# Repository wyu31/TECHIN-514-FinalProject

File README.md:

# TECHIN-514-FinalProject
This GitHub repository is for my TECHIN-514 final project and all my related files will be uploaded and updated to it.

## System Architecture with Diagram
### Slide 1 - Introduction
**Project Title**  
Finger Drumbeat

**Explanation**  
This is an IoT device set to add drum beats using hand gestures, allowing users to engage in existing music.

Generally, I want to achieve:
1. Different **fingertip accelerations** produce different **Stepper-motor-driven gauge needle** swing accelerations and different drum beat loudnesses (with **Speaker & Amplifier**).
2. Different **components of the drum** (Bass Drum, Tom-Tom Drum, Snare drum, Crash Cymbal, Ride Cymbal, Hi-Hat) are played under different **gestures**.
3. **OLED** screen displays the component currently being played.
4. **LED Array** randomly displays rhythm animation
5. **Button** can switch the random animations on the LED Array

**General Sketch**  

### Slide 2 - Sensor Device
In this part, the enclosure is divided into two parts: fingertip and wrist. The fingertip enclosure contains the MPU6050, and the wrist enclosure contains the ESP32 processor and battery.

MPU6050 and ESP32 will detect and analyze diffeerent fingertip accelerations for different needle swing accelerations and drumbeat volumes.

MPU6050 and ESP32 will also detect and analyze different gestures as different drum components (such as ass Drum, Tom-Tom Drum, Snare drum, Crash Cymbal, Ride Cymbal, Hi-Hat).

1. Sensor: MPU6050 accelerometer and gyroscope to detect hand accelerations and gestures
2. Processor: XIAO-ESP32-S3
3. Wireless link:  XIAO-ESP32-S3 has a bluetooth module inside
4. Power: Lithium Ion Polymer Battery Ideal For Feathers
5. Enclosure:(Shown on Sketch) 
6. Custom PCB: will be based on the sensor, battery & enclosure size

### Slide 3 - Display Device
The shaking acceleration of the stepper motor pointer depends on the acceleration of the finger; the intensity of the sound and enhanced sound also depends on the acceleration of the finger.

The LED array will randomly play flowing animations to reflect the linkage of audio and vision; touch the button to switch animations.

The OLED screen will display the names of the components of the drum set selected under the current gesture.

1. Stepper-motor-driven gauge needle:  Show the intensity and volume of the drumming. More forceful gestures could push the needle further, indicating a higher intensity and volume.
2. Processor: XIAO-ESP32-S3
3. LED Array:  LED Array randomly displays rhythm animation
4. Button: Capacitive touch button to switch animations
5. Enclosure:(Shown on Sketch) 
6. Custom PCB: will be based on the sensors & enclosure size
7. Battery: Lithium Ion Polymer Battery Ideal For Feathers
8. Displays: OLED - Text info of the type of drum sound currently selected

### Slide 4 - Figure & Diagram

**Device Communication Figure**

**Workflow Diagram**

**Display Device Arch**

## PCB Lab
### Processer: XIAO-ESP32-S3

### Sensor: XIAO-ESP32-S3

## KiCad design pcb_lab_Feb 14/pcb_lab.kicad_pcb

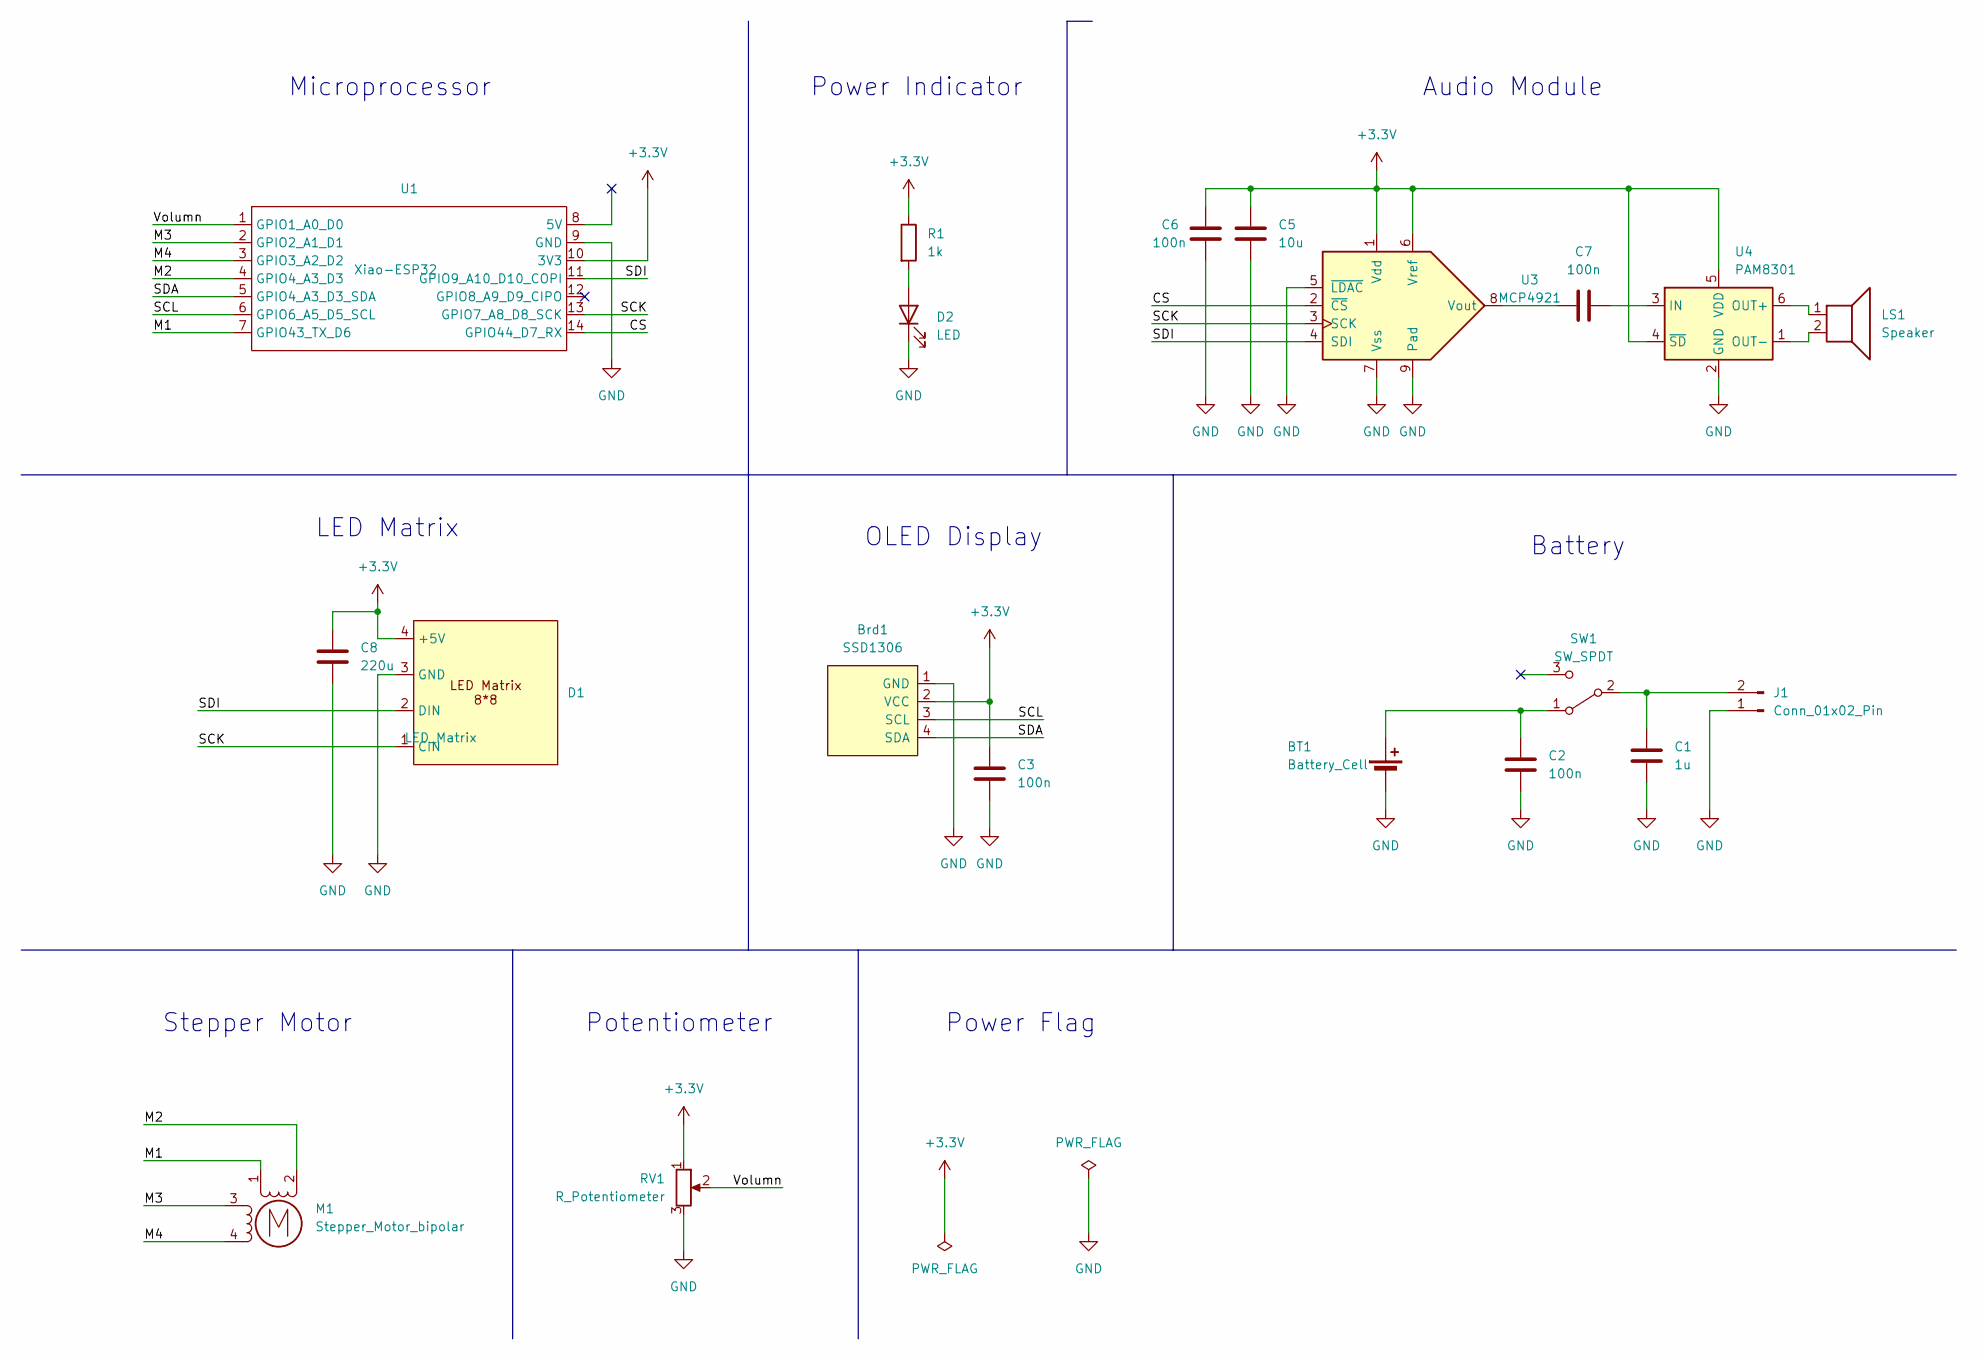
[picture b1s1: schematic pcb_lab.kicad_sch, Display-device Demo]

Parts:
BT1: Battery_Cell; JST_XA_B02B-XASK-1-A_1x02_P2.50mm_Vertical
Brd1: SSD1306; 128x64OLED
C1: 1u; C_0603_1608Metric_Pad1.08x0.95mm_HandSolder
C2, C3, C6, C7: 100n; C_0603_1608Metric_Pad1.08x0.95mm_HandSolder
C5: 10u; CP_EIA-1608-08_AVX-J_Pad1.25x1.05mm_HandSolder
C8: 220u; CP_Radial_D6.3mm_P2.50mm
D1: LED_Matrix; PinSocket_1x04_P2.54mm_Horizontal
D2: LED; LED_0603_1608Metric_Pad1.05x0.95mm_HandSolder
J1: Conn_01x02_Pin; JST_NV_B02P-NV_1x02_P5.00mm_Vertical
LS1: Speaker; JST_NV_B02P-NV_1x02_P5.00mm_Vertical
M1: Stepper_Motor_bipolar; X27_stepper_motor
R1: 1k; R_0603_1608Metric_Pad0.98x0.95mm_HandSolder
RV1: R_Potentiometer; Potentiometer_Piher_PC-16_Single_Horizontal
SW1: SW_SPDT; JST_EH_B3B-EH-A_1x03_P2.50mm_Vertical
U1: Xiao-ESP32; XIAO_ESP32_SENSE
U3: MCP4921; DFN-8-1EP_3x2mm_P0.5mm_EP1.3x1.5mm
U4: PAM8301; SOT-23-6

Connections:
+3.3V: Brd1.2 (VCC), C3.1, C5.1, C6.1, C8.1, D1.4 (+5V), R1.1, RV1.1, U1.10 (3V3), U3.1 (Vdd), U3.6 (Vref), U4.4 (~SD), U4.5 (VDD)
/CS: U1.14 (GPIO44_D7_RX), U3.2 (~CS)
/M1: M1.1, U1.7 (GPIO43_TX_D6)
/M2: M1.2 (-), U1.4 (GPIO4_A3_D3)
/M3: M1.3, U1.2 (GPIO2_A1_D1)
/M4: M1.4, U1.3 (GPIO3_A2_D2)
/SCK: D1.1 (CIN), U1.13 (GPIO7_A8_D8_SCK), U3.3 (SCK)
/SCL: Brd1.3 (SCL), U1.6 (GPIO6_A5_D5_SCL)
/SDA: Brd1.4 (SDA), U1.5 (GPIO4_A3_D3_SDA)
/SDI: D1.2 (DIN), U1.11 (GPIO9_A10_D10_COPI), U3.4 (SDI)
/Volumn: RV1.2, U1.1 (GPIO1_A0_D0)
GND: BT1.2 (-), Brd1.1 (GND), C1.2, C2.2, C3.2, C5.2, C6.2, C8.2, D1.3 (GND), D2.1 (K), J1.1, RV1.3, U1.9 (GND), U3.5 (~LDAC), U3.7 (Vss), U3.9 (Pad), U4.2 (GND)
unnamed: BT1.1 (+), C2.1, SW1.1 (A)
unnamed: D2.2 (A), R1.2
unnamed: C1.1, J1.2, SW1.2 (B)
unnamed: C7.1, U3.8 (Vout)
unnamed: C7.2, U4.3 (IN)
unnamed: LS1.1, U4.6 (OUT+)
unnamed: LS1.2, U4.1 (OUT-)

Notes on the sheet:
Audio Module
Power Flag
Stepper Motor
Microprocessor
Power Indicator
Battery
OLED Display
Potentiometer
LED Matrix

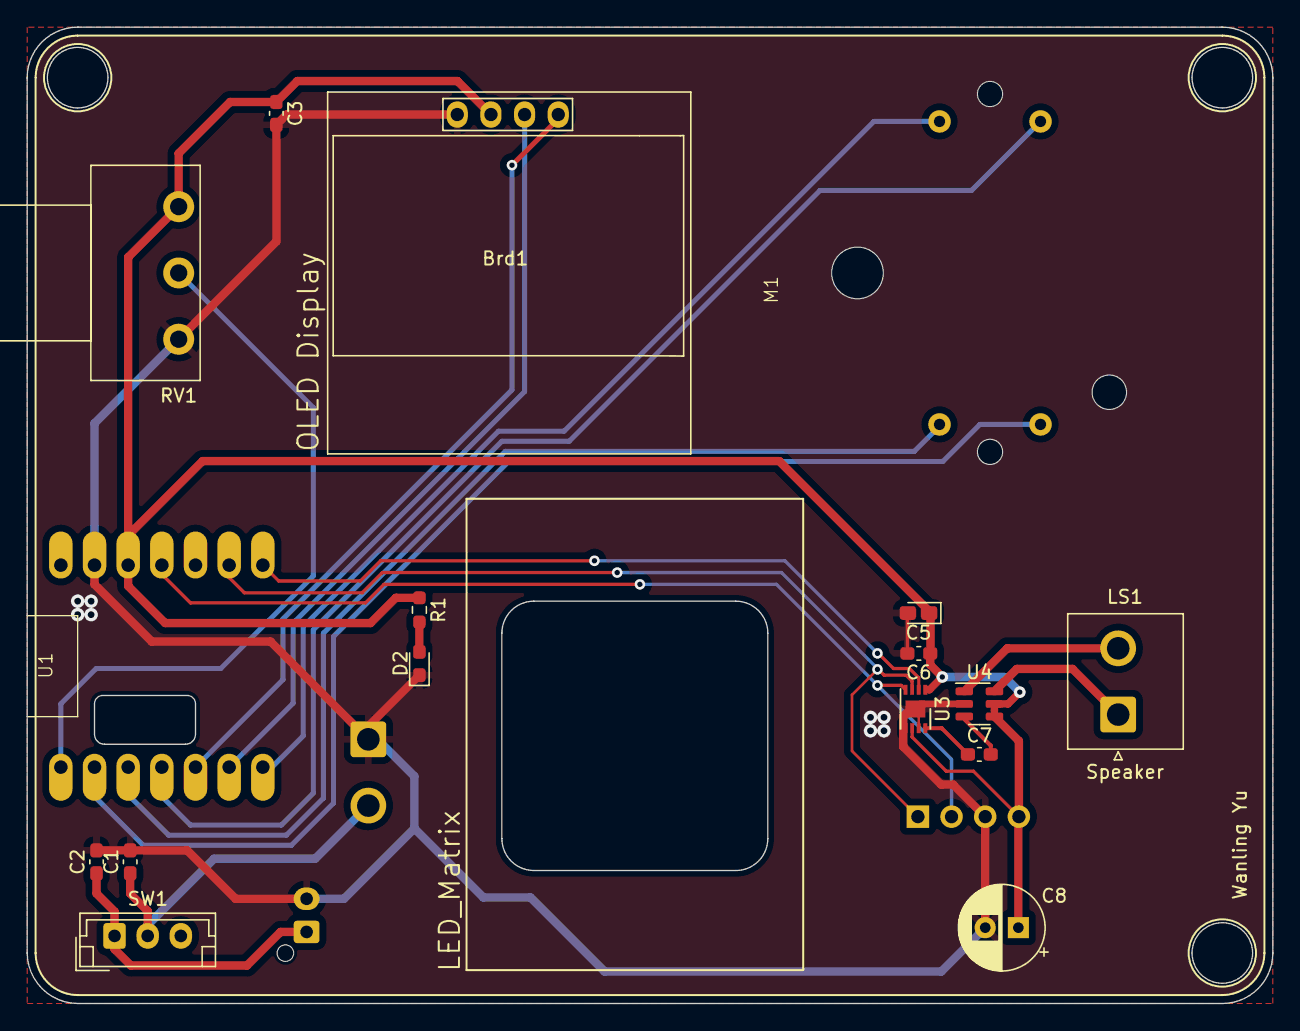
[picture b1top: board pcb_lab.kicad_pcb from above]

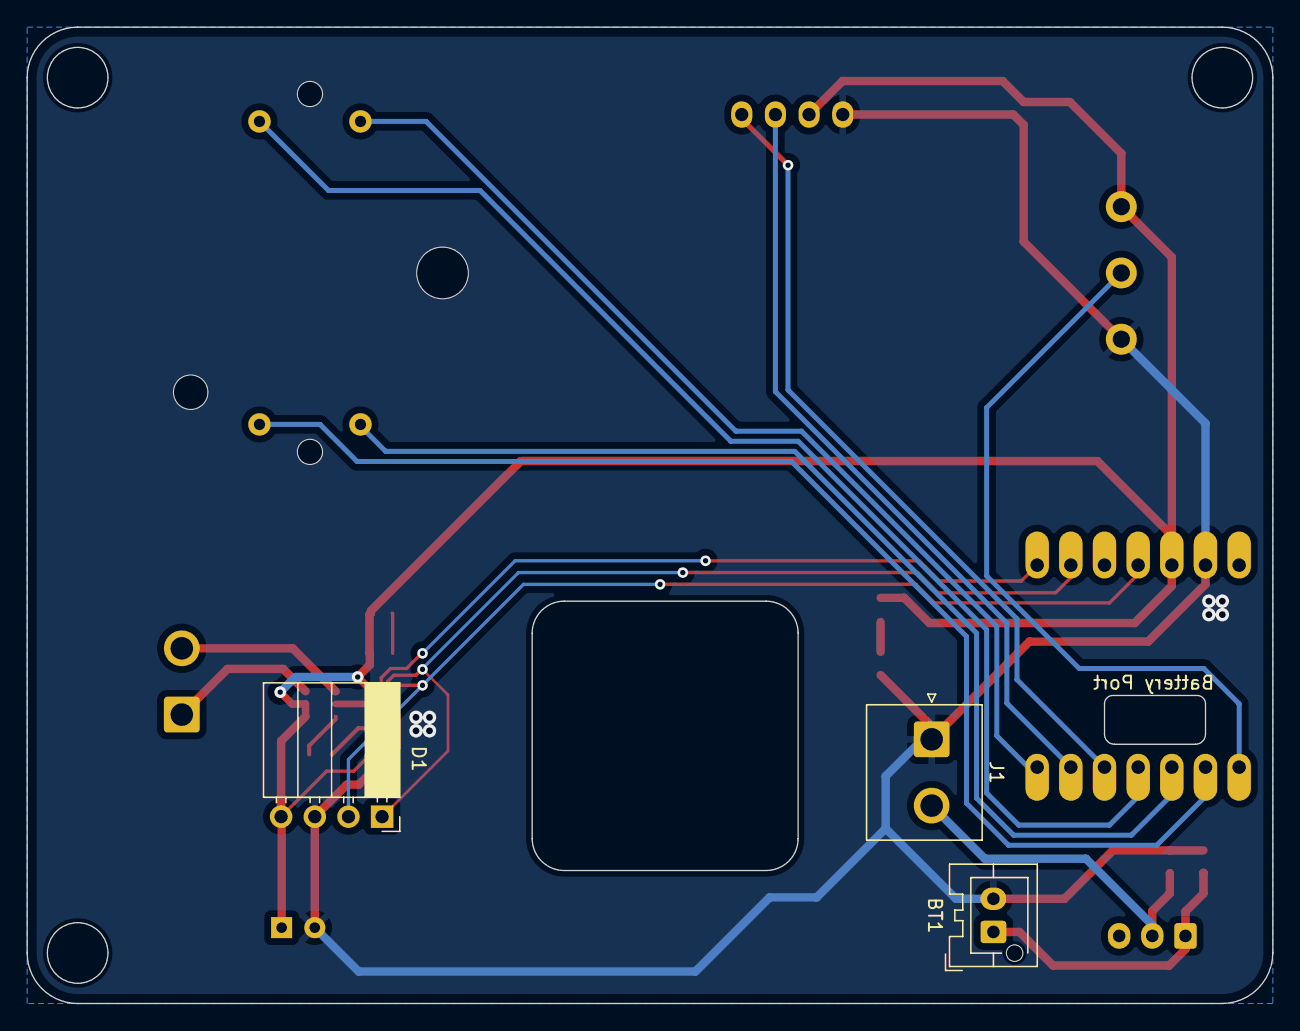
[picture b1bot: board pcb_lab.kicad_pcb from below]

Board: 2 copper layers, 94.0 x 73.7 mm, 20 parts (3 on the bottom side), 19 nets.

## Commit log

2024-01-17 Create the outline of the 4 slides
2024-01-17 Update the outline of the 4 slides
2024-01-17 main changes
2024-01-17 modify
2024-01-17 small modification of an image
2024-01-17 add .gitigonre
2024-01-18 Add pcb_lab related documents
2024-01-18 Modify pcb_lab related documents
2024-01-18 change an image
2024-01-19 Add the content about stepper motor diver breakout board
2024-02-07 update with battery estimate
2024-02-07 upload newest pcb design
2024-02-07 update arch
2024-02-08 update newest pcb design
2024-02-13 update 3D model
2024-02-13 update model
2024-02-21 updade 2nd device
2024-03-06 main updates
